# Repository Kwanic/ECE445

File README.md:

# Bilateral Earlobe Pulse Timing Measurement Device
**ECE 445 Senior Design Project - Spring 2026**

A custom PCB-based multi-channel physiological sensing platform for synchronized bilateral pulse transit time analysis. This project enables non-invasive cardiovascular monitoring by measuring pulse arrival time differences between left and right earlobes relative to ECG R-peaks.

---

## 🏆 Project Recognition
**Project #40**

This project demonstrates advanced biomedical sensing capabilities with sub-millisecond timing precision for bilateral cardiovascular dynamics research.

---

## 👥 Contributors

- **Zhikuan Zhang**
- **Joshua Joseph**
- **Mark Schmitt**

**Teaching Assistant:** Shiyuan Duan

---

## 📋 Problem Statement

Pulse arrival time (PAT) and pulse transit time (PTT) are widely studied non-invasive physiological metrics that reflect cardiovascular dynamics, vascular stiffness, and autonomic regulation. Conventional PTT systems measure the time delay between an ECG R-peak and a single peripheral photoplethysmography (PPG) waveform, but **do not enable synchronized bilateral comparisons** of pulse arrival times.

**Key Challenges:**
- Lack of low-cost hardware platforms with precise time synchronization
- Accurate bilateral PTT comparison requires **sub-millisecond alignment** between ECG and multiple PPG channels
- Existing research systems rely on independent sensors or software-based synchronization, introducing timing uncertainty
- No readily available tools for controlled bilateral pulse timing comparison between left and right earlobes

---

## 💡 Solution

Our system provides a **hardware-synchronized, three-channel physiological sensing platform** capable of simultaneously acquiring:

- **1 ECG channel** (cardiac timing reference from chest electrodes)
- **2 PPG channels** (synchronized left and right earlobe pulse waveforms)

### Key Design Features:
- ✅ **Low-noise analog front-end circuitry** for high-quality signal acquisition
- ✅ **Hardware-level time synchronization** using shared sampling clock architecture
- ✅ **Precise multi-channel ADC acquisition** with <1ms inter-channel timing jitter
- ✅ **Bluetooth Low Energy (BLE)** wireless data transmission
- ✅ **Sub-millisecond timing precision** for reliable bilateral pulse timing analysis

---

## 🎯 High-Level Requirements

1. **Microcontroller (nRF52840)** basic functions working normally:
   - Bluetooth Low Energy wireless connection
   - Data writing and reading
   - SPI communication
   - Charging system functioning properly

2. **MAX30003 ECG driver** functioning properly:
   - Collect ECG signals from any person
   - Display electrocardiogram dynamically via Bluetooth wireless transmission
   - ECG board fully operational

3. **Dual MAX86141 PPG drivers** working properly:
   - Drive LEDs to flash
   - Collect signals from photodiodes
   - Correctly plot PPG waveforms
   - Calculate PTT time difference between both earlobes

---

## 🔧 System Architecture

### Block Diagram
The system consists of three main PCB modules:

**ECG Board:**
- Power Subsystem (Battery → BMS → Voltage Regulator)
- ECG Analog Front-End Subsystem (Electrodes → Input Protection → MAX30003)
- Control Subsystem (nRF52840 + Timer/Timestamp)
- Wireless Subsystem (BLE Radio + 2.4GHz Antenna)

**PPG Boards (×2):**
- Power Subsystem (Battery → BMS → Voltage Regulator)
- Optical Sensing Subsystem (SFH-7050A LEDs + Photodiode → MAX86141)
- Control Subsystem (nRF52840 + Timer/Timestamp)
- Wireless Subsystem (BLE Radio + 2.4GHz Antenna)

All boards communicate wirelessly with a mobile device running a **PTT Calculator** app for real-time bilateral pulse timing analysis.

---

## 📐 Physical Design

- **Central wearable hub:** ~60mm × 40mm × 15mm
- **Two earlobe clips:** Spring-loaded design containing SFH-7050A optical sensors
- **ECG cable:** 3-lead configuration for chest placement
- **Battery-powered** with USB-C charging capability

---

## 📊 Technical Specifications

### Timing Accuracy Analysis
- **Sampling Rate:** 1000 Hz (1 ms period)
- **Quantization Uncertainty:** ±0.5 ms
- **Oscillator Drift:** 0.2 ms (±20 ppm over 10 seconds)
- **Inter-Channel Skew:** 0.01 ms
- **Total Timing Uncertainty:** ~0.71 ms ✅ (meets <1 ms requirement)

### Power Requirements
- **Regulated voltage:** 1.8V ± 0.2V DC from 3.7V LiPo battery
- **Voltage ripple:** <10 mV on MAX30003 AVDD pin
- **Total current draw:** <50 mA during active sensing
- **Battery life:** >10 hours on 500mAh battery

### Signal Quality
- **ECG:** 0.5–3 mV signal acquisition with R-peak detection
- **PPG:** >100 Hz sampling rate per channel
- **LED current:** Limited to 50% of max to prevent thermal discomfort

---

## 🛠️ Key Components

| Component | Part Number | Function |
|-----------|-------------|----------|
| Microcontroller | nRF52840-QFAA | BLE communication & data processing (×3) |
| ECG AFE | MAX30003CTI+ | Ultra-low power biopotential acquisition |
| PPG AFE | MAX86141 | Optical pulse sensing (×2) |
| Optical Sensor | SFH-7050A | LED + photodiode module (×2) |
| Power Management | NPM1100-QDAA-R7 | Battery charging & regulation (×3) |
| Voltage Regulators | TLV73318PDBVT, TLV76033DBZR | Low-noise power supply |

---

## 📱 Final Results

### ECG Board

### PPG Boards

### ECG Waveform Capture

---

## 🧪 Verification & Testing

### Power Subsystem
- ✅ Measure LDO output voltage under peak load (1.6V – 2V)
- ✅ Verify voltage ripple <10 mV using oscilloscope
- ✅ Confirm current draw <50 mA in Active Sensing Mode

### ECG Subsystem
- ✅ Verify 47kΩ safety resistors on electrode leads
- ✅ Confirm R-peak interrupt triggers within 5 ms
- ✅ Validate R-peaks distinguishable from T-waves and noise

### PPG Subsystem
- ✅ Verify dual-channel sampling >100 Hz using logic analyzer
- ✅ Confirm LED drive current settings via SPI registers
- ✅ Validate heart rate peaks visible in mobile app

### Data Acquisition
- ✅ Inject synchronized 1Hz pulse to verify <1 ms timestamp delta
- ✅ Test BLE connection stability at 3 meters distance
- ✅ Confirm hardware timestamps attached to transmitted data

---

## 🔬 Research Applications

This system enables investigation of:
- **Bilateral pulse arrival time differences** under various postural conditions
- **Head tilt effects** on cardiovascular timing
- **Asymmetric vascular conditions** that may indicate stroke risk
- **Autonomic regulation** through bilateral cardiovascular dynamics
- **Next-generation wearable health monitoring** technologies

⚠️ **Note:** This is a **research measurement tool**, not a clinical diagnostic device.

---

## 🛡️ Safety & Ethics

### Electrical Safety
- Battery-powered low-voltage operation
- Current-limiting protection on all electrode connections
- LED drive currents within manufacturer specifications
- Safe PCB design following medical device principles (IEC 60601 considerations)

### Data Privacy
- Anonymized physiological data collection
- Secure Bluetooth Low Energy transmission
- Limited storage access controls

### Research Compliance
- IRB approval obtained for human subject testing
- Clear communication of experimental device status
- Honest reporting of measurement accuracy and limitations per IEEE Code of Ethics

---

## 📅 Project Timeline

**Spring 2026 Schedule:**
- **Week 3/2:** PCB design & firmware initialization
- **Week 3/9:** Subsystem testing & breadboard demo
- **Week 3/23:** PPG & ECG integration
- **Week 3/30:** Software timing implementation
- **Week 4/6:** System integration & progress demo
- **Week 4/13:** Head-tilt verification testing & final demo preparation
- **Week 4/27:** Final presentation
- **Week 5/4:** Final report submission

---

## 🎤 Presentation

[View Project Presentation](https://docs.google.com/presentation/d/1ANw0dAJMYt3qXs6DZXwqXkPDi8zIwqQTNQY861npctc/edit?usp=sharing)

---

## 🎥 Demo

[Watch Project Demo](https://www.youtube.com/embed/-hJwNCSb4G8)

---

## 📚 References

- IEEE Code of Ethics: [www.ieee.org/about/corporate/governance/p7-8.html](https://www.ieee.org/about/corporate/governance/p7-8.html)
- Nordic Semiconductor nRF52840 Product Specification v1.11
- Analog Devices MAX30003 Datasheet Rev. 2
- Analog Devices MAX86141 Datasheet Rev. 5
- ams-OSRAM SFH 7050A BIOFY® Sensor Datasheet
- IEC 60601-1:2005+AMD1:2012 Medical Electrical Equipment Standards

---

## 🎓 Course Information

**University of Illinois Urbana-Champaign**
**ECE 445: Senior Design Project**
**Spring 2026**

---

## 📄 License

This project was completed as part of academic coursework at the University of Illinois. All design documents, schematics, and source code are for educational purposes.

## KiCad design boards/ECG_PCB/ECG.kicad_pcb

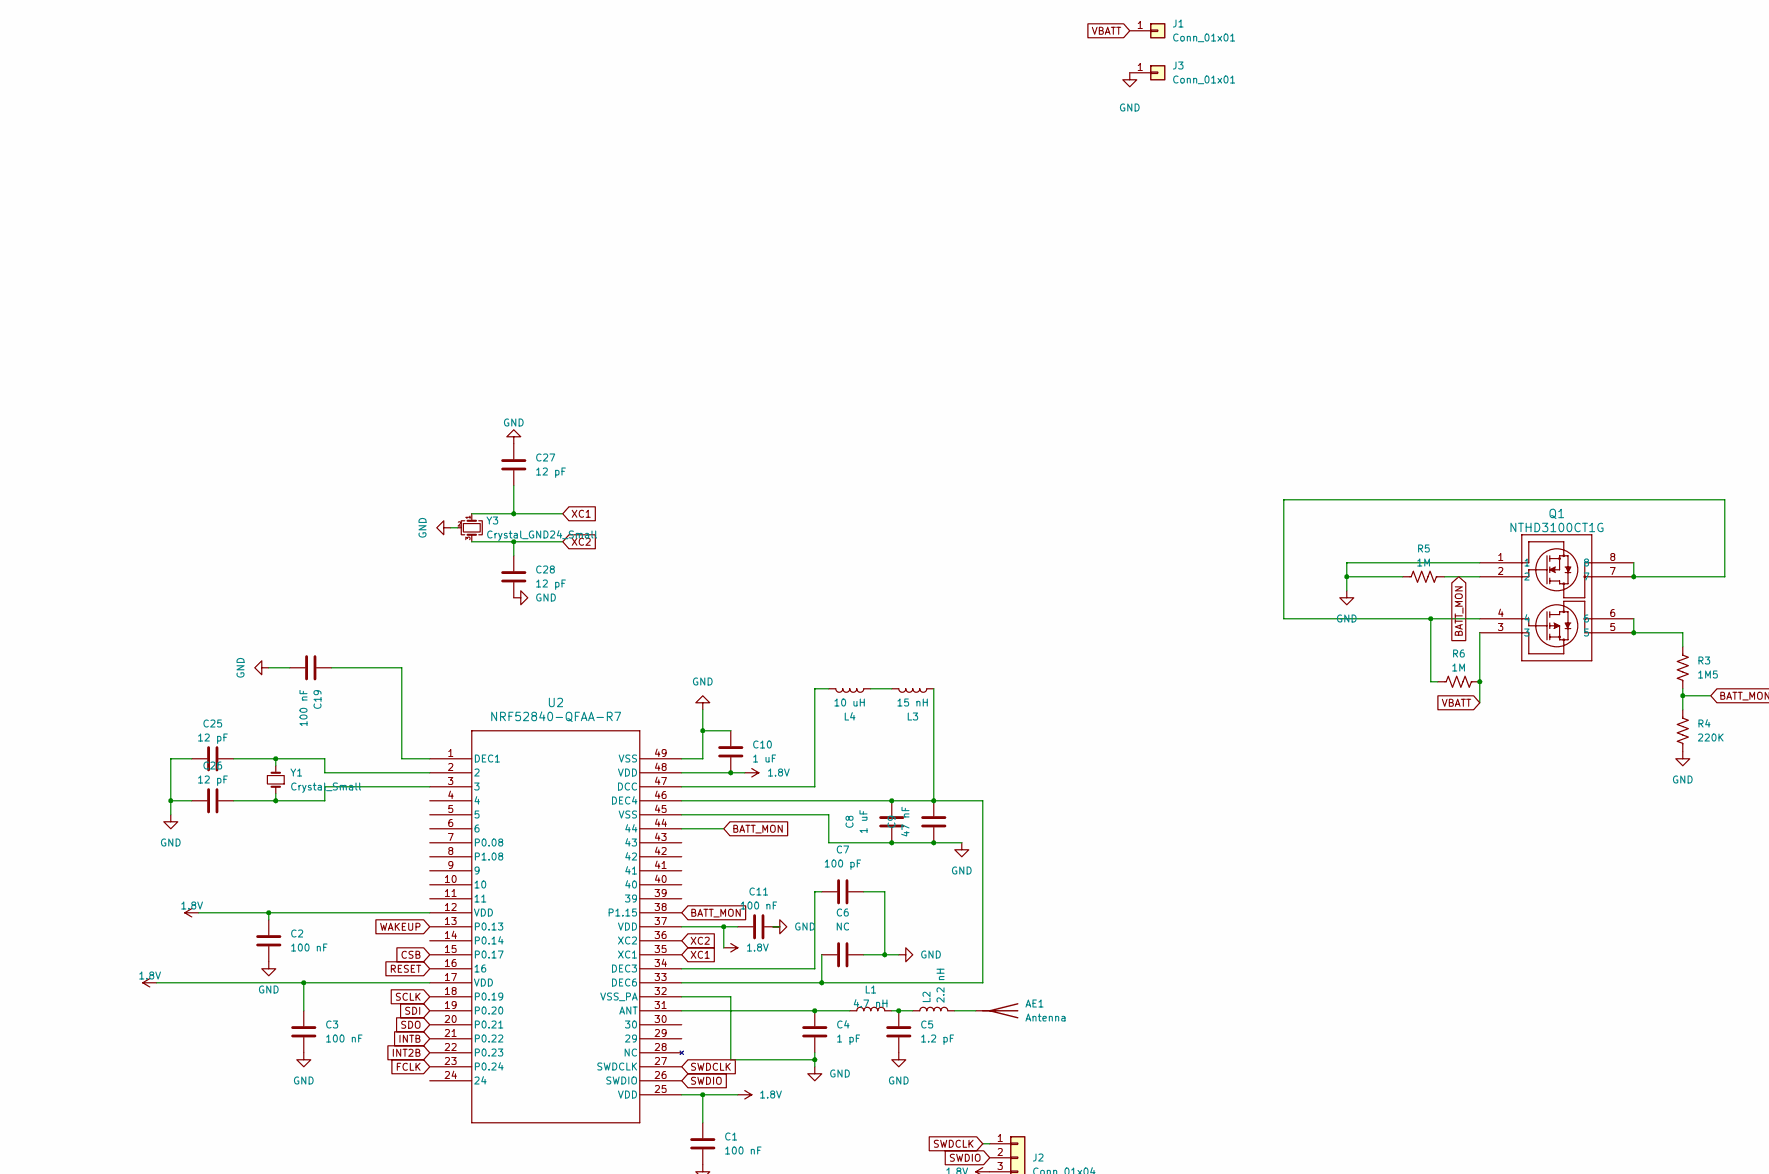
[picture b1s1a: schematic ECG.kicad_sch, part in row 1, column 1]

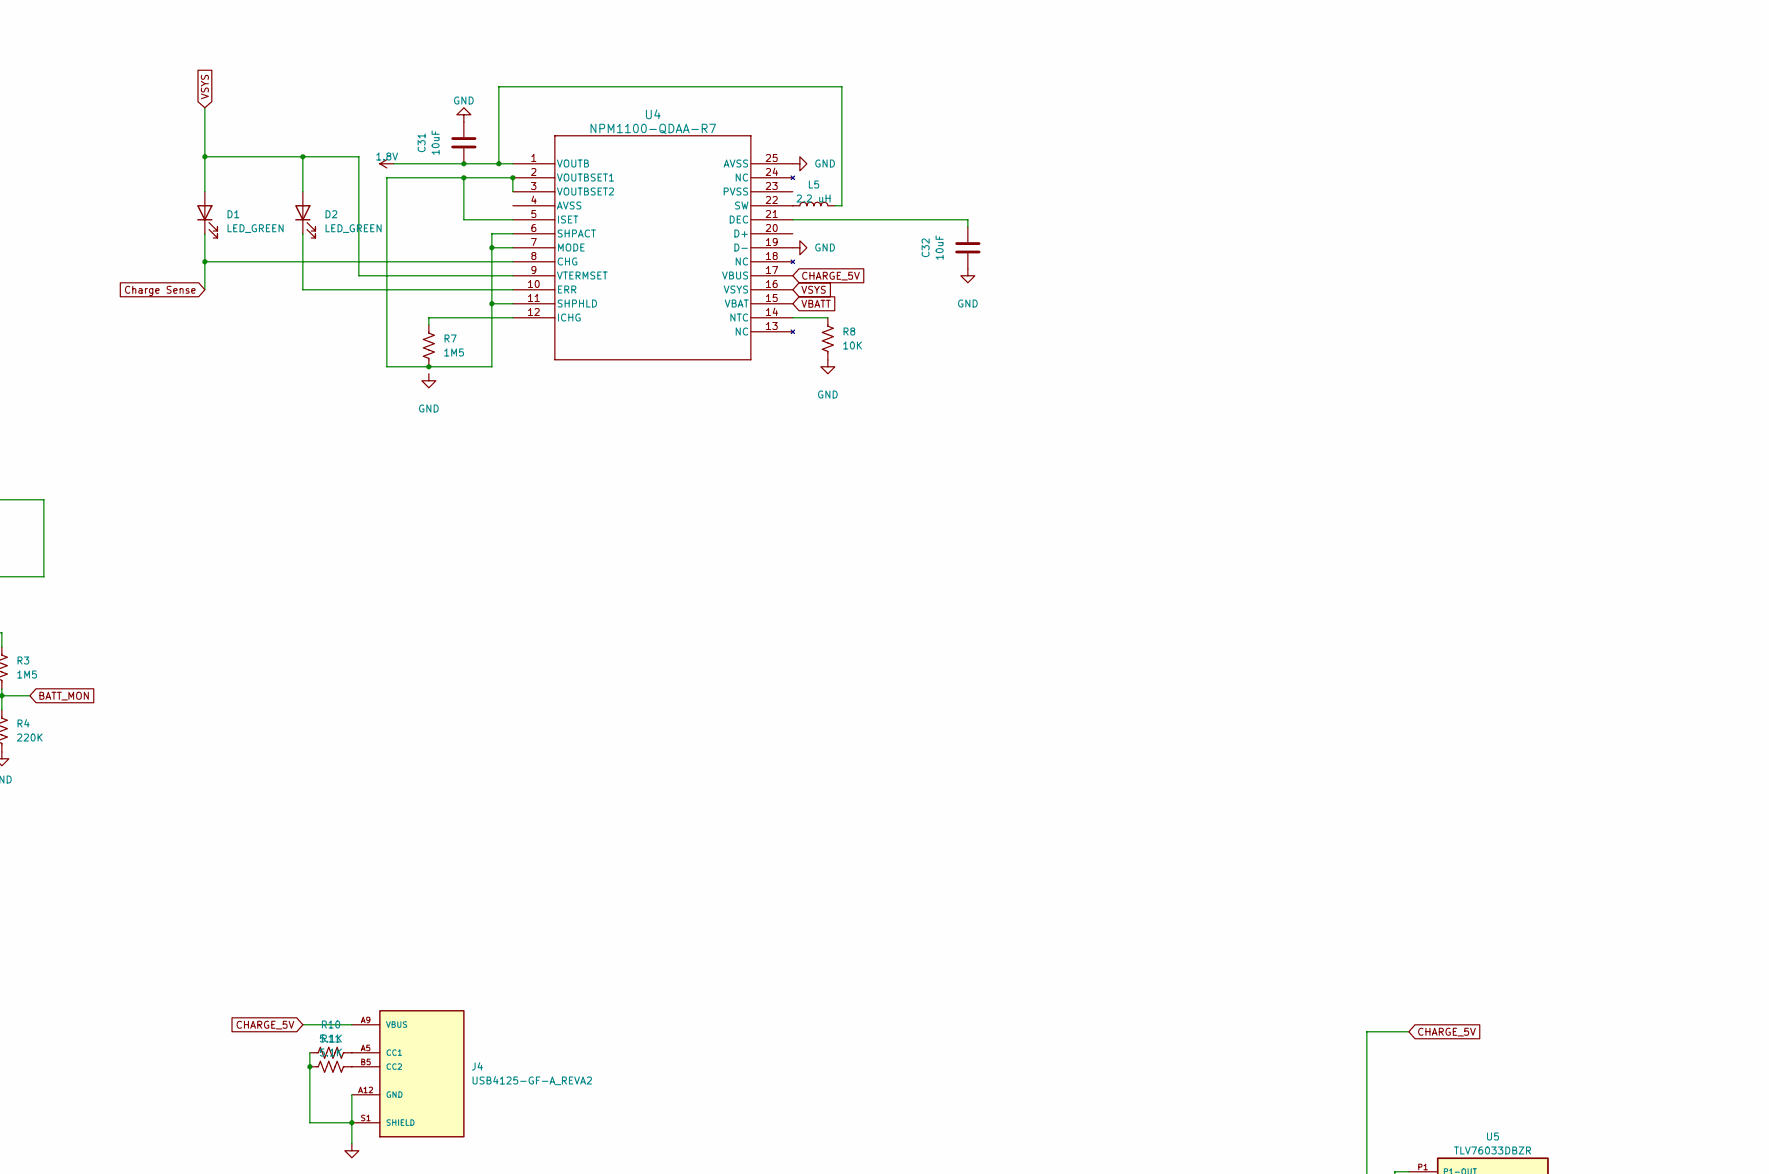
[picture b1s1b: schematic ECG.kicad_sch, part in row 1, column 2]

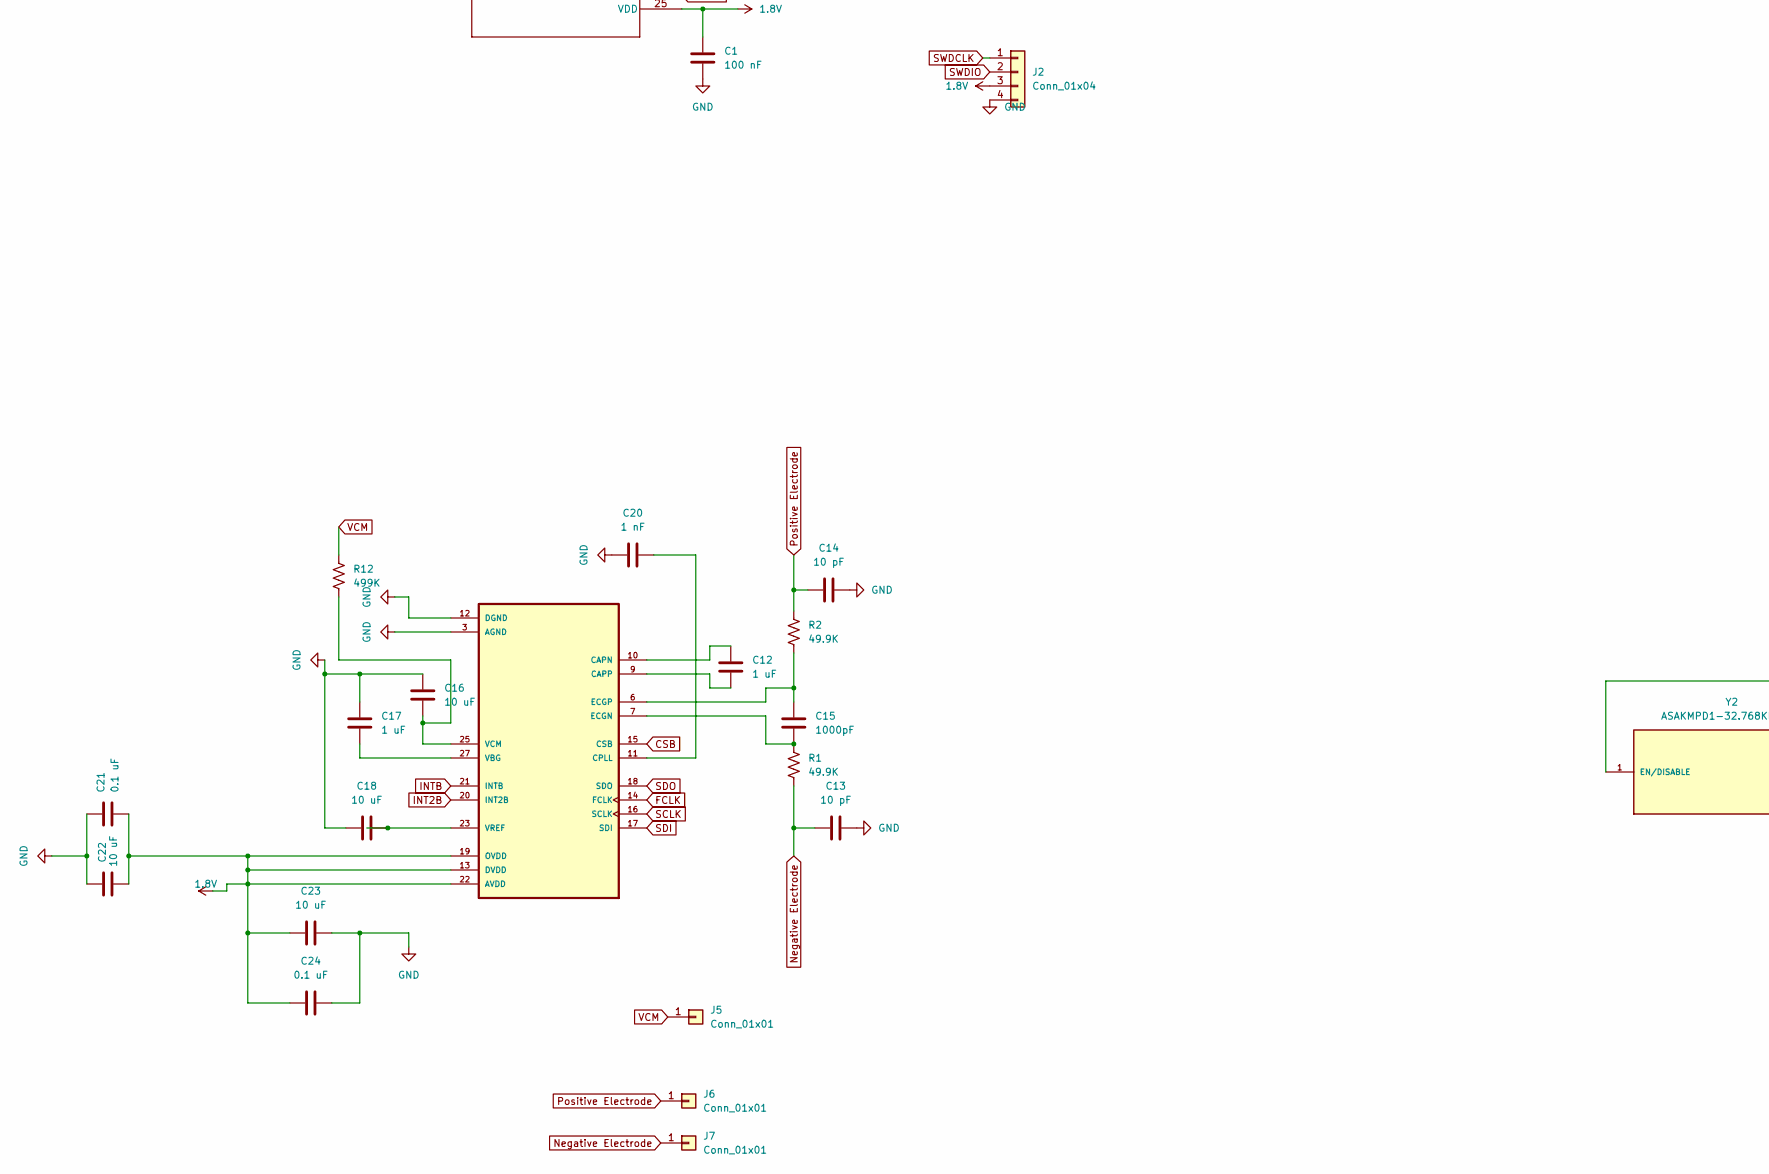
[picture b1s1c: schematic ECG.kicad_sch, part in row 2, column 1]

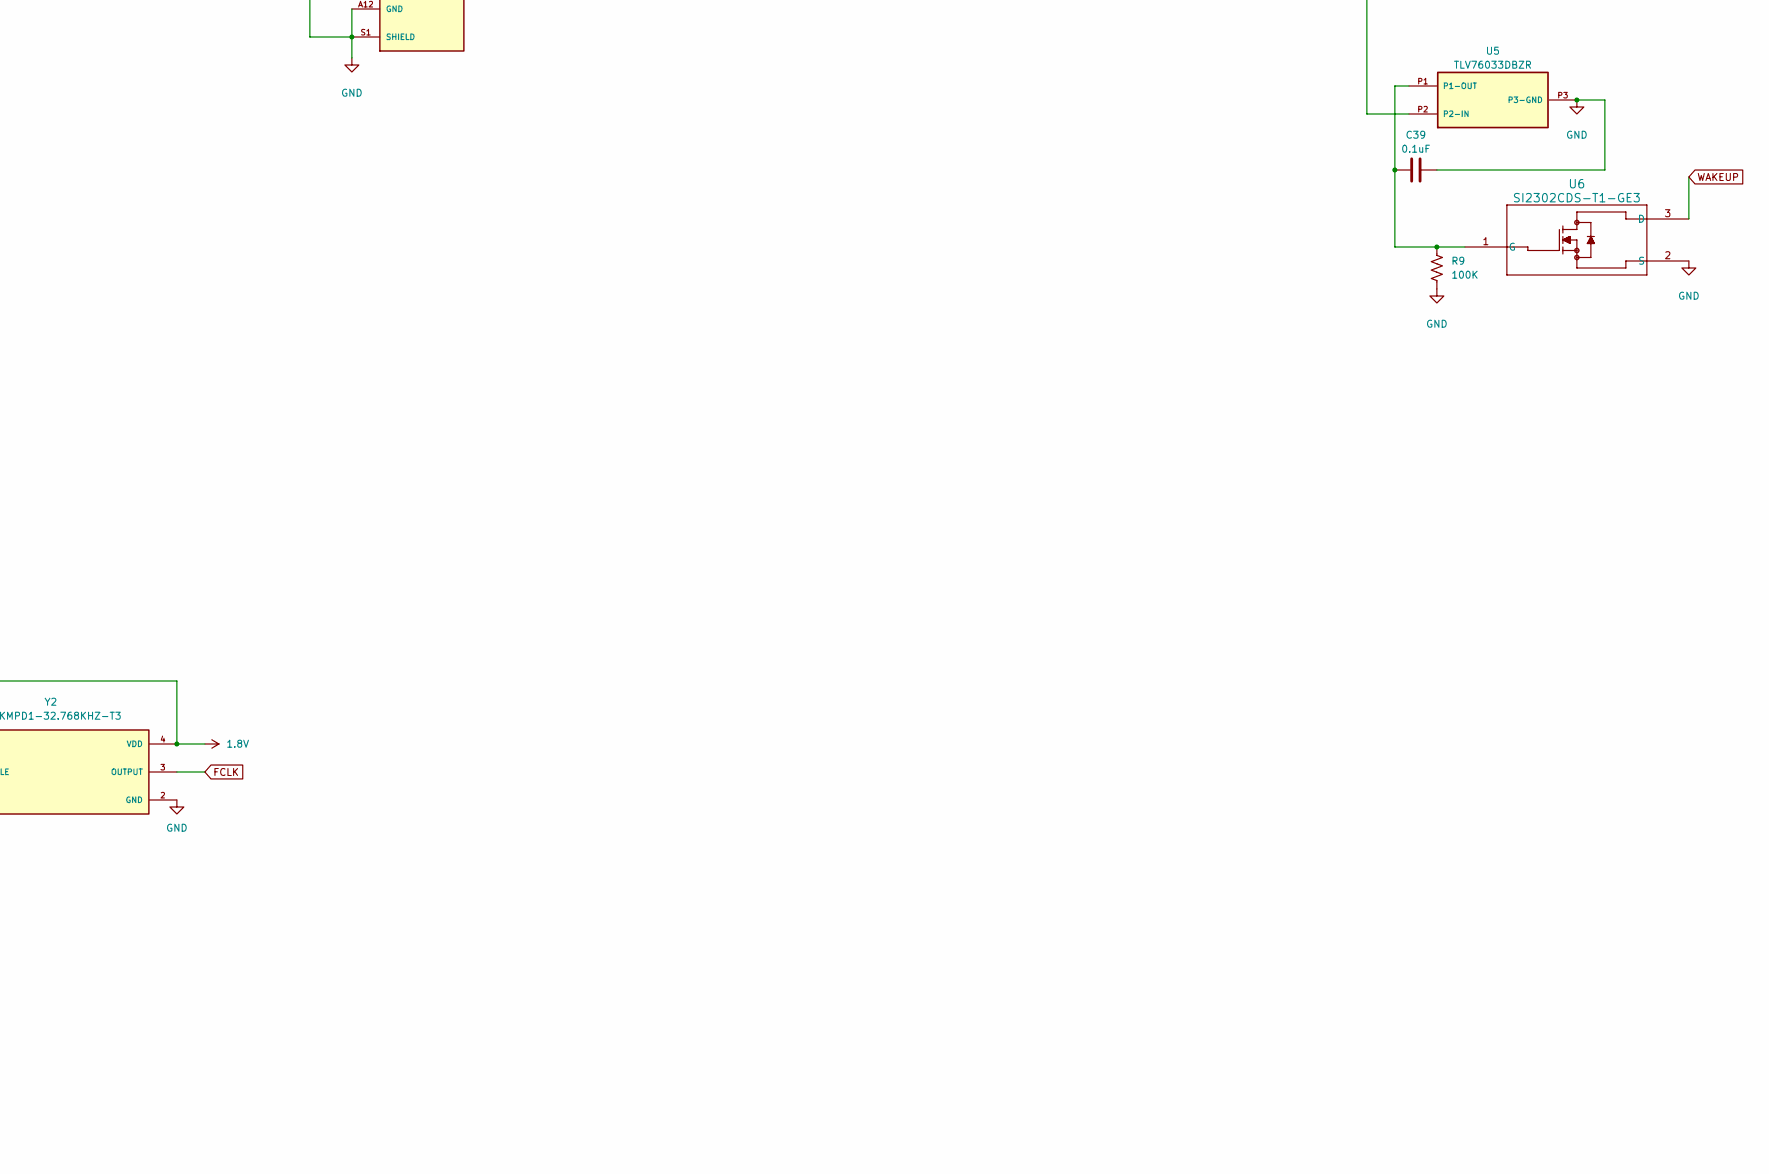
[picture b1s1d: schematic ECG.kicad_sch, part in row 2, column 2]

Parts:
AE1: Antenna; AMCA72-2R470G-S1F-T4
C1, C2, C3, C11, C19: 100 nF; C_0201_0603Metric_Pad0.64x0.40mm_HandSolder
C4: 1 pF; C_0201_0603Metric_Pad0.64x0.40mm_HandSolder
C5: 1.2 pF; C_0201_0603Metric_Pad0.64x0.40mm_HandSolder
C6: NC; C_0201_0603Metric
C7: 100 pF; C_0201_0603Metric_Pad0.64x0.40mm_HandSolder
C8, C10, C12, C17: 1 uF; C_0402_1005Metric_Pad0.74x0.62mm_HandSolder
C9: 47 nF; C_0201_0603Metric_Pad0.64x0.40mm_HandSolder
C13, C14: 10 pF; C_0402_1005Metric_Pad0.74x0.62mm_HandSolder
C15: 1000pF; C_0402_1005Metric_Pad0.74x0.62mm_HandSolder
C16, C18, C22, C23: 10 uF; C_0402_1005Metric_Pad0.74x0.62mm_HandSolder
C20: 1 nF; C_0402_1005Metric_Pad0.74x0.62mm_HandSolder
C21, C24: 0.1 uF; C_0402_1005Metric_Pad0.74x0.62mm_HandSolder
C25, C26, C27, C28: 12 pF; C_0201_0603Metric_Pad0.64x0.40mm_HandSolder
C31, C32: 10uF; C_0201_0603Metric_Pad0.64x0.40mm_HandSolder
C39: 0.1uF; C_0201_0603Metric_Pad0.64x0.40mm_HandSolder
D1, D2: LED_GREEN; LED_0805_2012Metric
J1, J3, J5, J6, J7: Conn_01x01; SolderWire-0.5sqmm_1x01_D0.9mm_OD2.1mm
J2: Conn_01x04; SolderWire-0.5sqmm_1x04_P4.6mm_D0.9mm_OD2.1mm
J4: USB4125-GF-A_REVA2; USB_C_Receptacle_GCT_USB4125-xx-x_6P_TopMnt_Horizontal; PARTREV Rev A2
L1: 4.7 nH; L_0201_0603Metric_Pad0.64x0.40mm_HandSolder
L2: 2.2 nH; L_0201_0603Metric_Pad0.64x0.40mm_HandSolder
L3: 15 nH; L_0201_0603Metric_Pad0.64x0.40mm_HandSolder
L4: 10 uH; L_0201_0603Metric_Pad0.64x0.40mm_HandSolder
L5: 2.2 uH; L_0201_0603Metric_Pad0.64x0.40mm_HandSolder
Q1: NTHD3100CT1G; SON8_CASE1206A-03_OSI
R1, R2: 49.9K; R_0402_1005Metric_Pad0.72x0.64mm_HandSolder
R3, R7: 1M5; R_0402_1005Metric_Pad0.72x0.64mm_HandSolder
R4: 220K; R_0402_1005Metric_Pad0.72x0.64mm_HandSolder
R5, R6: 1M; R_0402_1005Metric_Pad0.72x0.64mm_HandSolder
R8: 10K; R_0402_1005Metric_Pad0.72x0.64mm_HandSolder
R9: 100K; R_0402_1005Metric_Pad0.72x0.64mm_HandSolder
R10, R11: 5.1K; R_0402_1005Metric_Pad0.72x0.64mm_HandSolder
R12: 499K; R_0402_1005Metric_Pad0.72x0.64mm_HandSolder
U1: MAX30003CTI_; QFN50P500X500X80-29N
U2: NRF52840-QFAA-R7; QFN48_NRF52840-QFAA-R7_NOR
U4: NPM1100-QDAA-R7; QFN24_NPM1100_NOR
U5: TLV76033DBZR
U6: SI2302CDS-T1-GE3; TO-236_VIS
Y1: Crystal_Small; Crystal_SMD_MicroCrystal_CM9V-T1A-2Pin_1.6x1.0mm
Y2: ASAKMPD1-32.768KHZ-T3; ASAKMPD1_ABR; PARTREV 08.16.2018
Y3: Crystal_GND24_Small; XTAL_ECS-320-10-37B2-CKY-TR

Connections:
1.8V: C1.1, C2.1, C3.1, C10.1, C11.2, C21.2, C22.2, C23.1, C24.1, C31.1, J2.3, L5.2, U1.13 (DVDD), U1.19 (OVDD), U1.22 (AVDD), U2.12 (VDD), U2.17 (VDD), U2.25 (VDD), U2.37 (VDD), U2.48 (VDD), U4.1 (VOUTB), Y2.1 (EN/DISABLE), Y2.4 (VDD)
BATT_MON: Q1.2, R3.2, R4.1, R5.2, U2.38 (P1.15), U2.44
CHARGE_5V: J4.A9 (VBUS), J4.B9 (VBUS), U4.17 (VBUS), U5.P2 (P2-IN)
CSB: U1.15 (CSB), U2.15 (P0.17)
Charge Sense: D1.1 (K), U4.8 (CHG)
FCLK: U1.14 (FCLK), U2.23 (P0.24), Y2.3 (OUTPUT)
GND: C1.2, C2.2, C3.2, C4.2, C5.1, C6.2, C7.2, C8.1, C9.1, C10.2, C11.1, C13.2, C14.1, C16.1, C17.2, C18.1, C19.2, C20.1, C21.1, C22.1, C23.2, C24.2, C25.1, C26.1, C27.2, C28.1, C31.2, C32.1, C39.1, J2.4, J3.1, J4.A12 (GND), J4.B12 (GND), J4.S1 (SHIELD), J4.S2 (SHIELD), J4.S3 (SHIELD), J4.S4 (SHIELD), Q1.1, R4.2, R5.1, R8.2, R9.2, R10.1, R11.1, U1.3 (AGND), U1.8 (AGND), U1.12 (DGND), U1.28 (AGND), U1.29 (AGND), U2.32 (VSS_PA), U2.45 (VSS), U2.49 (VSS), U4.19 (D-), U4.25 (AVSS), U5.P3 (P3-GND), U6.2 (S), Y2.2 (GND), Y3.2 (G), Y3.4 (G)
INT2B: U1.20 (INT2B), U2.22 (P0.23)
INTB: U1.21 (INTB), U2.21 (P0.22)
Negative Electrode: C13.1, J7.1, R1.2
unnamed: AE1.1 (A), L2.2
unnamed: C5.2, L1.2, L2.1
unnamed: C25.2, U2.2, Y1.2
unnamed: C26.2, U2.3, Y1.1
unnamed: D2.1 (K), U4.10 (ERR)
unnamed: J4.A5 (CC1), R10.2
unnamed: J4.B5 (CC2), R11.2
unnamed: L3.2, L4.1
unnamed: Q1.4, Q1.7, Q1.8, R6.1
unnamed: Q1.5, Q1.6, R3.1
unnamed: C12.2, U1.10 (CAPN)
unnamed: C12.1, U1.9 (CAPP)
unnamed: C20.2, U1.11 (CPLL)
unnamed: C15.2, R1.1, U1.7 (ECGN)
unnamed: C15.1, R2.2, U1.6 (ECGP)
unnamed: C17.1, U1.27 (VBG)
unnamed: C16.2, R12.2, U1.25 (VCM)
unnamed: C18.2, U1.23 (VREF)
unnamed: C4.1, L1.1, U2.31 (ANT)
unnamed: L4.2, U2.47 (DCC)
unnamed: C19.1, U2.1 (DEC1)
unnamed: C7.1, U2.34 (DEC3)
unnamed: C6.1, C8.2, C9.2, L3.1, U2.33 (DEC6), U2.46 (DEC4)
unnamed: C32.2, U4.21 (DEC)
unnamed: R7.1, U4.12 (ICHG)
unnamed: R7.2, U4.2 (VOUTBSET1), U4.3 (VOUTBSET2), U4.5 (ISET), U4.6 (SHPACT), U4.7 (MODE), U4.11 (SHPHLD)
unnamed: R8.1, U4.14 (NTC)
unnamed: L5.1, U4.22 (SW)
unnamed: C39.2, R9.1, U5.P1 (P1-OUT), U6.1 (G)
Positive Electrode: C14.2, J6.1, R2.1
RESET: U2.16
SCLK: U1.16 (SCLK), U2.18 (P0.19)
SDI: U1.17 (SDI), U2.19 (P0.20)
SDO: U1.18 (SDO), U2.20 (P0.21)
SWDCLK: J2.1, U2.27 (SWDCLK)
SWDIO: J2.2, U2.26 (SWDIO)
VBATT: J1.1, Q1.3, R6.2, U4.15 (VBAT)
VCM: J5.1, R12.1
VSYS: D1.2 (A), D2.2 (A), U4.9 (VTERMSET), U4.16 (VSYS)
WAKEUP: U2.13 (P0.13), U6.3 (D)
XC1: C27.1, U2.35 (XC1), Y3.1
XC2: C28.2, U2.36 (XC2), Y3.3

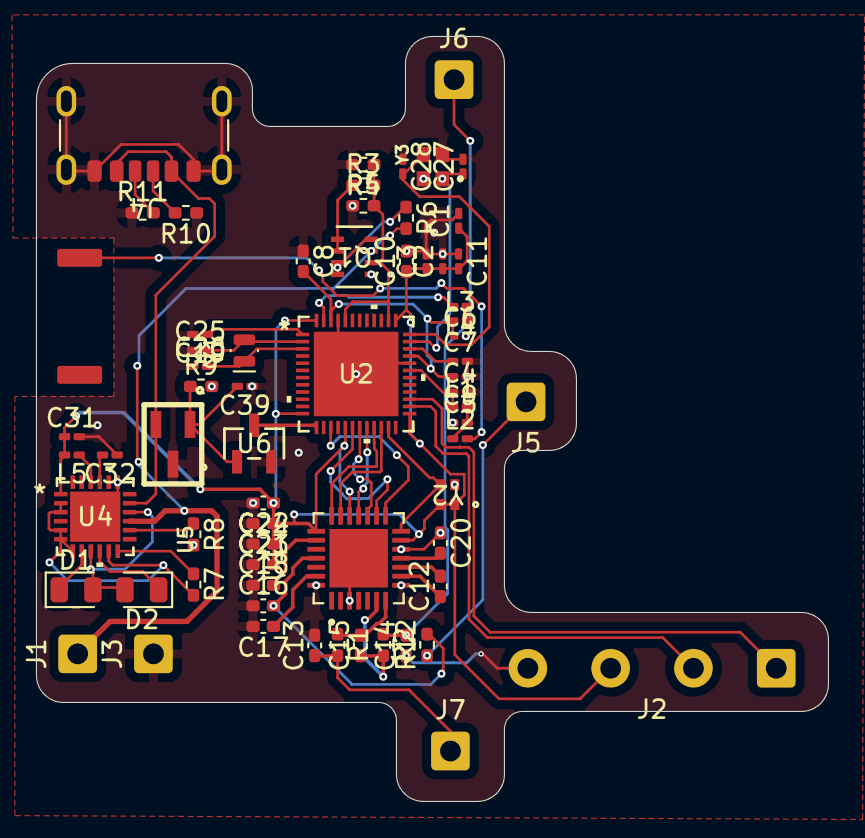
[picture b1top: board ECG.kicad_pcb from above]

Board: 2 copper layers, 44.0 x 42.5 mm, 67 parts (0 on the bottom side), 51 nets.

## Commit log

2026-05-03 final
2026-05-06 Create labnotebook
2026-05-06 Rename labnotebook to README.md
2026-05-06 Fix image paths in README.md
    Updated image paths in README.md to remove 'images/' prefix.
2026-05-07 mark notebook
